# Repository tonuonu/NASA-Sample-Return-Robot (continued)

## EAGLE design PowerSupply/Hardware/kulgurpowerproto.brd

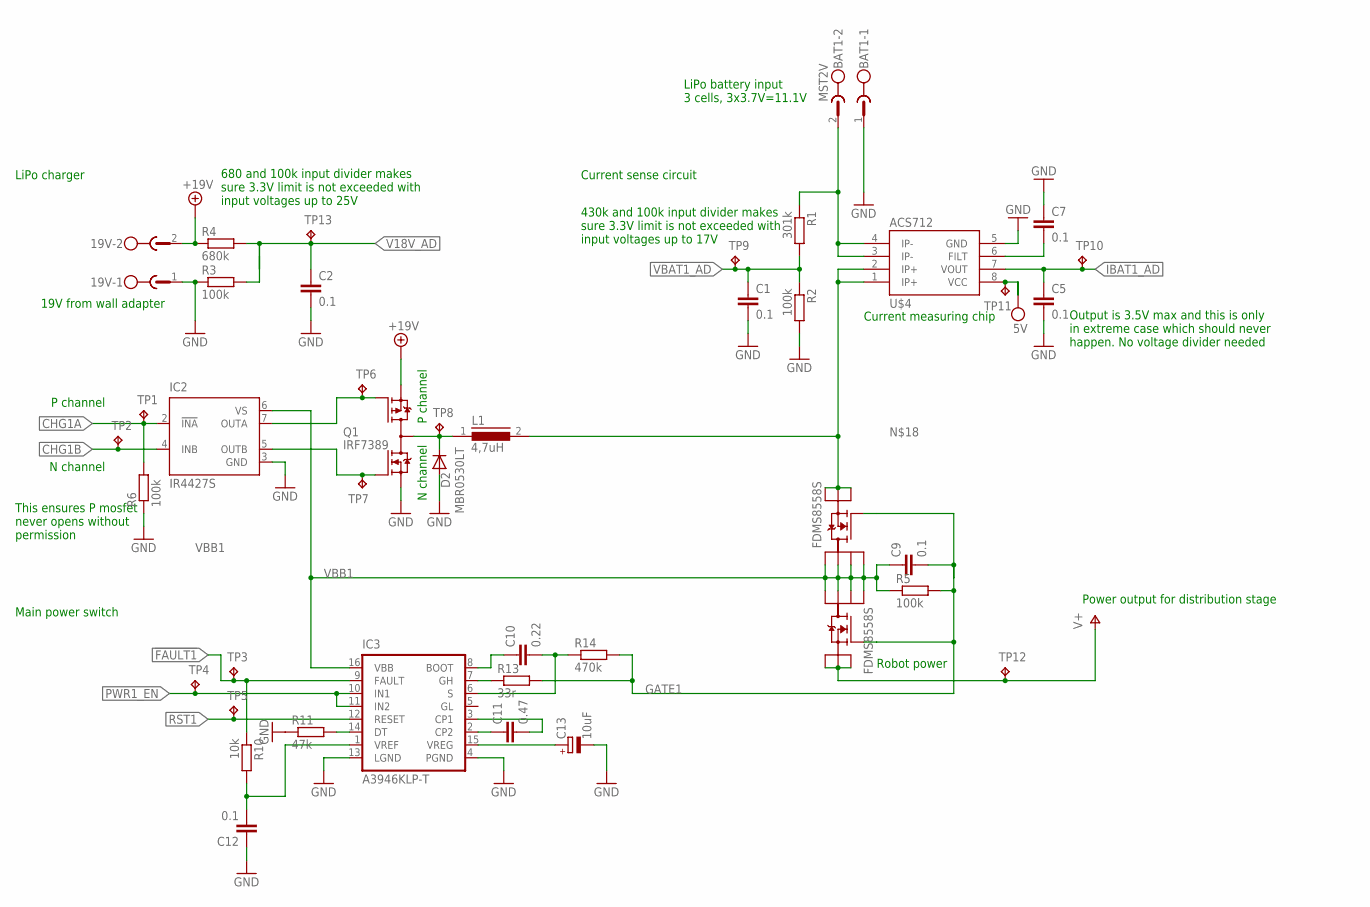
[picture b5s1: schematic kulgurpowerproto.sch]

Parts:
19V: MST2V; MSTBV2
BAT1: MST2V; MSTBV2
C1, C2, C5, C7, C9, C12: 0.1; C0603
C10: 0.22; C0603
C11: 0.47; C0603
C13: 10uF; A/3216-18R
D2: MBR0530LT; SOD123
IC2: IR4427S; SO08
IC3: A3946KLP-T; TSSOP16E
L1: 4,7uH; DR73
Q1: IRF7389; SO08-IRF
R1: 301k; R0603
R2, R3, R5, R6: 100k; R0603
R4: 680k; R0603
R10: 10k; R0603
R11: 47k; R0603
R13: 33r; R0603
R14: 470k; R0603
TP1, TP2, TP3, TP4, TP5, TP6, TP7, TP8, TP9, TP10, TP11, TP12, TP13: TPB2,54; B2,54
U$2, U$3: FDMS8558S; POWER56
U$4: ACS712; SO08

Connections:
5V: TP11.TP, U$4.8 (VCC)
!FAULT1: IC3.9 (FAULT), R10.1, TP3.TP
+19V: 19V.2, Q1.3 (P-S), R4.1
CHG1A: IC2.2 (!INA), R6.2, TP1.TP
CHG1B: IC2.4 (INB), TP2.TP
GATE1: C9.2, R5.2, R13.2, R14.2, U$2.P$4 (G), U$3.P$4 (G)
GND: 19V.1, BAT1.1, C1.2, C2.2, C5.2, C7.1, C12.1, C13.-, D2.A, IC2.3 (GND), IC3.4 (PGND), IC3.13 (LGND), Q1.1 (N-S), R2.2, R3.1, R6.1, R11.1, U$4.5 (GND)
IBAT1_AD: C5.1, TP10.TP, U$4.7 (VOUT)
unnamed: IC2.7 (OUTA), Q1.4 (P-G), TP6.TP
unnamed: IC2.5 (OUTB), Q1.2 (N-G), TP7.TP
unnamed: D2.C, L1.1, Q1.5 (D), Q1.6 (D), Q1.7 (D), Q1.8 (D), TP8.TP
unnamed: C10.1, IC3.8 (BOOT)
unnamed: L1.2, U$2.P$1 (S1), U$2.P$2 (S2), U$2.P$3 (S3), U$4.1 (IP+), U$4.2 (IP+)
unnamed: C10.2, IC3.6 (S), R14.1
unnamed: C7.2, U$4.6 (FILT)
unnamed: BAT1.2, R1.1, U$4.3 (IP-), U$4.4 (IP-)
unnamed: C11.1, IC3.2 (CP2)
unnamed: C11.2, IC3.3 (CP1)
unnamed: C12.2, IC3.1 (VREF), R10.2
unnamed: IC3.7 (GH), R13.1
unnamed: IC3.14 (DT), R11.2
unnamed: C13.+, IC3.15 (VREG)
PWR1_EN: IC3.10 (IN1), IC3.11 (IN2), TP4.TP
RST1: IC3.12 (RESET), TP5.TP
V18V_AD: C2.1, R3.2, R4.2, TP13.TP
V+: TP12.TP, U$3.P$1 (S1), U$3.P$2 (S2), U$3.P$3 (S3)
VBAT1_AD: C1.1, R1.2, R2.1, TP9.TP
VBB1: C9.1, IC2.6 (VS), IC3.16 (VBB), R5.1, U$2.P$5 (D4), U$2.P$6 (D3), U$2.P$7 (D2), U$2.P$8 (D1), U$3.P$5 (D4), U$3.P$6 (D3), U$3.P$7 (D2), U$3.P$8 (D1)

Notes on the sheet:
19V from wall adapter
LiPo battery input 3 cells, 3x3.7V=11.1V
Current measuring chip
Robot power
680 and 100k input divider makes sure 3.3V limit is not exceeded with input voltages up to 25V
430k and 100k input divider makes sure 3.3V limit is not exceeded with input voltages up to 17V
Output is 3.5V max and this is only in extreme case which should never happen. No voltage divider needed
LiPo charger
Current sense circuit
Main power switch
N channel
P channel
This ensures P mosfet never opens without permission
Power output for distribution stage

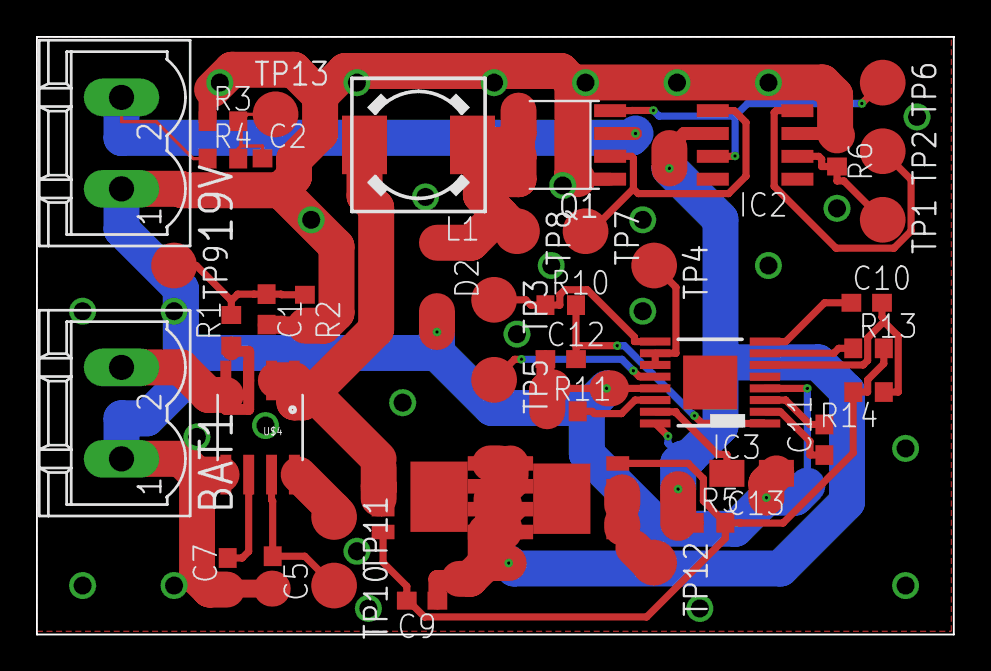
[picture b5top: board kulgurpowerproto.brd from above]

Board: 2 copper layers, 50.9 x 33.2 mm, 42 parts (0 on the bottom side), 28 nets.

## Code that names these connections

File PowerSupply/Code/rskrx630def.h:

/* Copyright (C) 2012 Renesas Electronics Corporation. All rights reserved.    */
/* Description   : Defines macros relating to the RX630 user LEDs and switches
*******************************************************************************/
/* Multiple inclusion prevention macro */
#ifndef _RSKRX630_H
#define _RSKRX630_H

/* Defines RX630 port registers */
#include "iorx630.h"

/* General Values */
#define SET_BIT_HIGH  (1)
#define SET_BIT_LOW    (0)
#define SET_BYTE_HIGH  (0xFF)
#define SET_BYTE_LOW  (0x00)

/* Switch port pins state settings */
#define  SW1          PORT3.PIDR.BIT.3
#define  SW2          PORT3.PIDR.BIT.2
#define  SW3          PORT3.PIDR.BIT.1
#define  SW4          PORT3.PIDR.BIT.0

/* LED ouptut pin settings */
#define  LED0      PORT2.PODR.BIT.B0
#define  LED1      PORT2.PODR.BIT.B1
#define  LED2      PORT2.PODR.BIT.B2
#define  LED3      PORT2.PODR.BIT.B3
#define  LED4      PORT2.PODR.BIT.B4
#define  LED5      PORT2.PODR.BIT.B5
#define  LED6      PORT2.PODR.BIT.B6
#define  LED7      PORT2.PODR.BIT.B7

/* LED data direction */
#define LED0_PORT_DIR  PORT2.PDR.BIT.B0
#define LED1_PORT_DIR  PORT2.PDR.BIT.B1
#define LED2_PORT_DIR  PORT2.PDR.BIT.B2
#define LED3_PORT_DIR  PORT2.PDR.BIT.B3
#define LED4_PORT_DIR  PORT2.PDR.BIT.B4
#define LED5_PORT_DIR  PORT2.PDR.BIT.B5
#define LED6_PORT_DIR  PORT2.PDR.BIT.B6
#define LED7_PORT_DIR  PORT2.PDR.BIT.B7

#define LED_GRN_PORT_DIR  PORT1.PDR.BIT.B3
#define LED_BLU_PORT_DIR  PORT1.PDR.BIT.B5
#define LED_RED_PORT_DIR  PORT1.PDR.BIT.B7

#define BAT0_EN PORTA.PODR.BIT.B7
#define BAT1_EN PORTB.PODR.BIT.B1
#define BAT2_EN PORTB.PODR.BIT.B2
#define BAT3_EN PORTB.PODR.BIT.B3
#define MAX1614_OFF  0
#define MAX1614_ON   1

#define BAT0_EN_DIR PORTA.PDR.BIT.B7
#define BAT1_EN_DIR PORTB.PDR.BIT.B1
#define BAT2_EN_DIR PORTB.PDR.BIT.B2
#define BAT3_EN_DIR PORTB.PDR.BIT.B3

#define PGOOD1_DIR PORT1.PDR.BIT.B9
#define PGOOD2_DIR PORTC.PDR.BIT.B2

#define PGOOD1 PORTC.PIDR.BIT.B3
#define PGOOD2 PORTC.PIDR.BIT.B2

#define OUT1_EN_DIR PORTB.PDR.BIT.B5
#define OUT2_EN_DIR PORTB.PDR.BIT.B7
#define OUT3_EN_DIR PORTJ.PDR.BIT.B3
#define OUT4_EN_DIR PORT5.PDR.BIT.B3
#define OUT5_EN_DIR PORT0.PDR.BIT.B7

#define OUT1_EN PORTB.PODR.BIT.B5
#define OUT2_EN PORTB.PODR.BIT.B7
#define OUT3_EN PORTJ.PODR.BIT.B3
#define OUT4_EN PORT5.PODR.BIT.B3
#define OUT5_EN PORT0.PODR.BIT.B7

#define SKIP0  PORTA.PODR.BIT.B1
#define SKIP1  PORTA.PODR.BIT.B2
#define SKIP2  PORTA.PODR.BIT.B3
#define SKIP3  PORTA.PODR.BIT.B5

#define SKIP0_DIR  PORTA.PDR.BIT.B1
#define SKIP1_DIR  PORTA.PDR.BIT.B2
#define SKIP2_DIR  PORTA.PDR.BIT.B3
#define SKIP3_DIR  PORTA.PDR.BIT.B5

/* Delay units */
#define uS        'u'
#define mS        'm'

/* End of multiple inclusion prevention macro */
#endif

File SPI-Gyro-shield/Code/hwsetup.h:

/*
 *  Copyright (c) 2013 Tonu Samuel
 *  All rights reserved.
 *
 *  This file is part of robot "Kuukulgur".
 *
 *  This is free software: you can redistribute it and/or modify
 *  it under the terms of the GNU General Public License as published by
 *  the Free Software Foundation, either version 3 of the License, or
 *  (at your option) any later version.
 *
 *  This is distributed in the hope that it will be useful,
 *  but WITHOUT ANY WARRANTY; without even the implied warranty of
 *  MERCHANTABILITY or FITNESS FOR A PARTICULAR PURPOSE.  See the
 *  GNU General Public License for more details.
 *
 *  You should have received a copy of the GNU General Public License
 *  along with this software.  If not, see <http://www.gnu.org/licenses/>.
 *
 */

#define myCKPOL (0)
#define myCKPH (1)
#define myIOPOL (1)

#define PD_INPUT    (0)
#define PD_OUTPUT   (1)
#define PF_TIMER    (1)
#define PF_MOTOR    (2)
#define PF_UART     (3)
#define PF_ANALOG   (0x80)

void HardwareSetup(void);

#define LED1         p1_0
#define LED1d        pd1_0
#define LED2         p1_1
#define LED2d        pd1_1
#define LED3         p1_2
#define LED3d        pd1_2
#define LED4         p1_3
#define LED4d        pd1_3
#define LED5         p1_4
#define LED5d        pd1_4

#define RESET0       p0_3
#define RESET0d      pd0_3
#define RESET1       p0_0
#define RESET1d      pd0_0
#define RESET2       p0_2
#define RESET2d      pd0_2
#define RESET3       p0_1
#define RESET3d      pd0_1

#define CDONE0       p0_7
#define CDONE1       p0_4
#define CDONE2       p0_6
#define CDONE3       p0_5

#define MOTOR_ERROR   p5_6
#define MOTOR_ERRORd   pd5_6

#define RESET5       p8_2
#define RESET5d      pd8_2


// SPI0, motor 0
#define CS0d         pd6_0
#define CS0          p6_0
#define CS0s         p6_0s
#define CLOCK0       p6_1
#define CLOCK0d      pd6_1
#define CLOCK0s      p6_1s
#define RX0          p6_2
#define RX0s         p6_2s
#define TX0          p6_3
#define TX0s         p6_3s
#define TX0d         pd6_3

// SPI3, motor 1
#define CS1d         pd4_0
#define CS1          p4_0
#define CS1s         p4_0s
#define CLOCK3       p4_1
#define CLOCK3d      pd4_1
#define CLOCK3s      p4_1s
#define RX3          p4_2
#define RX3s         p4_2s
#define RX3d         pd4_2
#define TX3          p4_3
#define TX3s         p4_3s
#define TX3d         pd4_3

// SPI4, motor 2
#define CS2         p9_4
#define CS2d        pd9_4
#define CLOCK4      p9_5
#define CLOCK4d     pd9_5
#define CLOCK4s     p9_5s
#define RX4         p9_7
#define RX4s        p9_7s
#define TX4         p9_6
#define TX4s        p9_6s
#define TX4d        pd9_6

// SPI6, motor 3
#define CS3d         pd7_3
#define CS3          p7_3
#define CS3s         p7_3s
#define CLOCK6       p4_5
#define CLOCK6d      pd4_5
#define CLOCK6s      p4_5s
#define RX6          p4_6
#define RX6s         p4_6s
#define RX6d         pd4_6
#define TX6          p4_7
#define TX6s         p4_7s
#define TX6d         pd4_7

// Serial 5

#define CS5         p8_4
#define CS5d        pd8_4
#define CS5s        p8_4s
#define CLOCK5      p7_7
#define CLOCK5d     pd7_7
#define CLOCK5s     p7_7s

#define TX5         p7_6
#define TX5s        p7_6s
#define TX5d        pd7_6
#define RX5         p8_0
#define RX5d        pd8_0
#define RX5s        p8_0s
#define TX5         p7_6
#define TX5d        pd7_6
#define TX5s        p7_6s

#define M0TX        u0tb
#define M1TX        u3tb
#define M2TX        u4tb
#define M3TX        u6tb

#define M0RX        u0rb
#define M1RX        u3rb
#define M2RX        u4rb
#define M3RX        u6rb


#define SPI_DELAY (1)


// Serial 1 (debug output)

#define TX1         p6_7
#define TX1s        p6_7s
#define TX1d        pd6_7
#define RX1         p6_6
#define RX1d        pd6_6
#define RX1s        p6_6s


struct statuses {
    char sek_flag;
};
void Read_AD(void);

extern volatile struct statuses status;
extern unsigned int base_freq;

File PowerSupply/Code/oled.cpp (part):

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#include "rskrx630def.h"

void Write_Data(unsigned char dat) {
    OLED_DC=1;
    OLED_DATA_PORT=dat;
    OLED_WR=0;
    __delay_cycles(24UL); // 0.250us
    OLED_WR=1;
    __delay_cycles(24UL); // 0.250us
    return;
}

void Write_Instruction(unsigned char cmd) {
    OLED_DC=0;
    OLED_DATA_PORT=cmd;
    OLED_WR=0;
    __delay_cycles(24UL); // 0.250us
    OLED_WR=1;
    __delay_cycles(24UL); // 0.250us
    return;
}
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
void
OLED_Set_Column_Address(unsigned char a, unsigned char b) {
    OLED_CS = 0;
    Write_Instruction(0x15);				   // Set Column Address
    Write_Data(a);					   //   Default => 0x00
    Write_Data(b);					   //   Default => 0x77
    OLED_CS = 1;
}

void
OLED_Set_Row_Address(unsigned char a, unsigned char b) {
    OLED_CS = 0;
    Write_Instruction(0x75);				   // Set Row Address
    Write_Data(a);					   //   Default => 0x00
    Write_Data(b);					   //   Default => 0x7F
    OLED_CS = 1;
}

void
OLED_Set_Write_RAM() {
    OLED_CS = 0;
    Write_Instruction(0x5C);				   // Enable MCU to Write into RAM
// omit!    OLED_CS = 1;
}

void
OLED_Set_Read_RAM() {
    OLED_CS = 0;
    Write_Instruction(0x5D);				   // Enable MCU to Read from RAM
// omit!    OLED_CS = 1;
}

void
OLED_Set_Remap_Format(unsigned char d) {
    OLED_CS = 0;
    Write_Instruction(0xA0);				   // Set Re-Map / Dual COM Line Mode
    Write_Data(d);					   //   Default => 0x40
    //     Horizontal Address Increment
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    //     Scan from COM0 to COM[N-1]
    //     Disable COM Split Odd Even
    Write_Data(0x11);				   //   Default => 0x01 (Disable Dual COM Mode)
    OLED_CS = 1;
}
void

OLED_Set_Start_Line(unsigned char d) {
    OLED_CS = 0;
    Write_Instruction(0xA1);				   // Set Vertical Scroll by RAM
    Write_Data(d);					   //   Default => 0x00
    OLED_CS = 1;
}

void
OLED_Set_Display_Offset(unsigned char d) {
    OLED_CS = 0;
    Write_Instruction(0xA2);				   // Set Vertical Scroll by Row
    Write_Data(d);					   //   Default => 0x00
    OLED_CS = 1;
}

void
OLED_Set_Display_Mode(unsigned char d) {
    OLED_CS = 0;
    Write_Instruction(0xA4 | d);				   // Set Display Mode
    //   Default => 0xA4
    //     0xA4 (0x00) => Entire Display Off, All Pixels Turn Off
    //     0xA5 (0x01) => Entire Display On, All Pixels Turn On at GS Level 15
    //     0xA6 (0x02) => Normal Display
    //     0xA7 (0x03) => Inverse Display
    OLED_CS = 1;
}

void
OLED_Set_Partial_Display(unsigned char a, unsigned char b, unsigned char c) {
    OLED_CS = 0;
    Write_Instruction(0xA8 | a);				   // Default => 0x8F
    //   Select Internal Booster at Display On
    if (a == 0x00) {
	Write_Data(b);
	Write_Data(c);
    }
    OLED_CS = 1;
}

void
OLED_Set_Function_Selection(unsigned char d) {
    OLED_CS = 0;
    Write_Instruction(0xAB);				   // Function Selection
    Write_Data(d);					   //   Default => 0x01
    //     Enable Internal VDD Regulator
    OLED_CS = 1;
}

void
OLED_Set_Display_On_Off(unsigned char d) {
    OLED_CS = 0;
    Write_Instruction(0xAE | d);				   // Set Display On/Off
    //   Default => 0xAE
    //     0xAE (0x00) => Display Off (Sleep Mode On)
    //     0xAF (0x01) => Display On (Sleep Mode Off)
    OLED_CS = 1;
}

void
OLED_Set_Phase_Length(unsigned char d) {
    OLED_CS = 0;
    Write_Instruction(0xB1);				   // Phase 1 (Reset) & Phase 2 (Pre-Charge) Period Adjustment
    Write_Data(d);					   //   Default => 0x74 (7 Display Clocks [Phase 2] / 9 Display Clocks [Phase 1])
    //     D[3:0] => Phase 1 Period in 5~31 Display Clocks
    //     D[7:4] => Phase 2 Period in 3~15 Display Clocks
    OLED_CS = 1;
}

void
OLED_Set_Display_Clock(unsigned char d) {
    OLED_CS = 0;
    Write_Instruction(0xB3);				   // Set Display Clock Divider / Oscillator Frequency
    Write_Data(d);					   //   Default => 0xD0
    //     A[3:0] => Display Clock Divider
    //     A[7:4] => Oscillator Frequency
    OLED_CS = 1;
}

void
OLED_Set_Display_Enhancement_A(unsigned char a, unsigned char b) {
    OLED_CS = 0;
    Write_Instruction(0xB4);				   // Display Enhancement
    Write_Data(0xA0 | a);				   //   Default => 0xA2
    //     0xA0 (0x00) => Enable External VSL
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    Write_Data(0x05 | b);				   //   Default => 0xB5
    //     0xB5 (0xB0) => Normal
    //     0xFD (0xF8) => Enhance Low Gray Scale Display Quality
    OLED_CS = 1;
}

void
OLED_Set_GPIO(unsigned char d) {
    OLED_CS = 0;
    Write_Instruction(0xB5);				   // General Purpose IO
    Write_Data(d);					   //   Default => 0x0A (GPIO Pins output Low Level.)
    OLED_CS = 1;
}

void
OLED_Set_Precharge_Period(unsigned char d) {
    OLED_CS = 0;
    Write_Instruction(0xB6);				   // Set Second Pre-Charge Period
    Write_Data(d);					   //   Default => 0x08 (8 Display Clocks)
    OLED_CS = 1;
}

void
OLED_Set_Precharge_Voltage(unsigned char d) {
    OLED_CS = 0;
    Write_Instruction(0xBB);				   // Set Pre-Charge Voltage Level
    Write_Data(d);					   //   Default => 0x17 (0.50*VCC)
    OLED_CS = 1;
}

void
OLED_Set_VCOMH(unsigned char d) {
    OLED_CS = 0;
    Write_Instruction(0xBE);				   // Set COM Deselect Voltage Level
    Write_Data(d);					   //   Default => 0x04 (0.80*VCC)
    OLED_CS = 1;
}

void
OLED_Set_Contrast_Current(unsigned char d) {
    OLED_CS = 0;
    Write_Instruction(0xC1);				   // Set Contrast Current
    Write_Data(d);					   //   Default => 0x7F
    OLED_CS = 1;
}

void
OLED_Set_Master_Current(unsigned char d) {
    OLED_CS = 0;
    Write_Instruction(0xC7);				   // Master Contrast Current Control
    Write_Data(d);					   //   Default => 0x0f (Maximum)
    OLED_CS = 1;
}

void
OLED_Set_Multiplex_Ratio(unsigned char d) {
    OLED_CS = 0;
    Write_Instruction(0xCA);				   // Set Multiplex Ratio
    Write_Data(d);					   //   Default => 0x7F (1/128 Duty)
    OLED_CS = 1;
}

void
OLED_Set_Display_Enhancement_B(unsigned char d) {
    OLED_CS = 0;
    Write_Instruction(0xD1);				   // Display Enhancement
    Write_Data(0x82 | d);				   //   Default => 0xA2
    //     0x82 (0x00) => Reserved
    //     0xA2 (0x20) => Normal
    Write_Data(0x20);
    OLED_CS = 1;
}

void
OLED_Set_Command_Lock(unsigned char d) {
    OLED_CS = 0;
    Write_Instruction(0xFD);				   // Set Command Lock
    Write_Data(0x12 | d);				   //   Default => 0x12
    //     0x12 => Driver IC interface is unlocked from entering command.
    //     0x16 => All Commands are locked except 0xFD.
    OLED_CS = 1;
}
const static unsigned int width = 256;
const static unsigned int height = 64;
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    unsigned int i, j;
    OLED_Set_Column_Address(OLED_Shift + a, OLED_Shift + b );
    OLED_Set_Row_Address(0,OLED_Max_Row );
    OLED_CS = 0;
    OLED_Set_Write_RAM();

    for (i = 0; i <height ; i++) { /* row */
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              Write_Data(pic[i*(width/2)+j]);
	}
    }
    OLED_CS = 1;
}

//-=-=-=-=-=-=-=-=-=-=-=-=-=-=-=-=-=-=-=-=-=-=-=-=-=-=-=-=-=-=-=-=-=-=-=
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    unsigned char i, j;
    OLED_Set_Column_Address(0x00, 0x77);
    OLED_Set_Row_Address(0x00, 0x7F);
    OLED_CS = 0;
    OLED_Set_Write_RAM();
    for (i = 0; i < 128; i++) {
	for (j = 0; j < 120; j++) {
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	    Write_Data(Data);
	}
    }
    OLED_CS = 1;
}

//-=-=-=-=-=-=-=-=-=-=-=-=-=-=-=-=-=-=-=-=-=-=-=-=-=-=-=-=-=-=-=-=-=-=-=
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    unsigned char i, j;
    OLED_Set_Column_Address(OLED_Shift + a, OLED_Shift + b);
    OLED_Set_Row_Address(c, d);
    OLED_CS = 0;
    OLED_Set_Write_RAM();
    for (i = 0; i < (d - c + 1); i++) {
	for (j = 0; j < (b - a + 1); j++) {
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	    Write_Data(Data);
	}
    }
    OLED_CS = 1;
}
#if 0
//-=-=-=-=-=-=-=-=-=-=-=-=-=-=-=-=-=-=-=-=-=-=-=-=-=-=-=-=-=-=-=-=-=-=-=
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	}
	OLED_Set_Column_Address(OLED_Shift + c, OLED_Shift + c);
	OLED_Set_Row_Address(d, d + 7);
        OLED_CS = 0;
	OLED_Set_Write_RAM();
        n=1;
        for (p = 0; p < 8; p++){
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            Write_Data(Font);
            n<<=1;
        }
        OLED_CS = 1;
	c++;
    }
    OLED_Set_Remap_Format(0x14);
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    ENABLE_PWR=1; /* Enable TPS51222. 
                   * Basically 5V is enabled to ACS712 current sensors
                   */
    OUT4_EN = 1; // Configure TPS51222 DC DC outputs
    OUT5_EN = 1; // 1 is enable, 0 is disable
#endif
    
    
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#if 1
    if(SWITCHHOLD_1 & gSwitchFlag) {
        if(OUT4_EN == 1 && ENABLE_PWR==1) {
            OUT4_EN=0;
            OUT5_EN=0;
           // ENABLE_PWR=0;
        } else if(ENABLE_PWR==0) {
            ENABLE_PWR=1;
        } else {
            OUT4_EN = 1;
            OUT5_EN = 1;
            gSwitchFlag &= (SWITCHPRESS_ALL | ~SWITCHHOLD_1);
            gSwitchFlag |= SWITCHPRESS_1;
        }
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    OLED_RD_PORT_DIR=1;
    OLED_RESET_PORT_DIR=1;
    PORTD.PDR.BYTE=0xFF;
    OLED_CS=1;
    OLED_WR=1;
    OLED_RD=1;

    OLED_RESET = 0;    
    __delay_cycles(100UL*2000UL); // 2000us delay - required in datasheet
    OLED_RESET = 1;
    __delay_cycles(100UL*2000UL); // 2000us delay    

    OLED_Set_Command_Lock(0x12);			   // Unlock Basic Commands (0x12/0x16)
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
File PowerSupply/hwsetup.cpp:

/* Copyright (C) 2012 Renesas Electronics Corporation. All rights reserved.   */
/*******************************************************************************
* File Name    : hwsetup.c
* Version     : 1.00
* Device     : R5F5630E
* Tool-Chain   : Renesas RX Toolchain 1.2.0.0
* H/W Platform  : RSKRX630
* Description   : Defines the hardware initialisation routines used each time 
*          the MCU is restarted. 
*******************************************************************************/
/*******************************************************************************
* History     : 23 Jan. 2012  Ver. 1.00 First Release
*******************************************************************************/

/*******************************************************************************
System Includes
*******************************************************************************/
/* Includes assembley level definitions */
#include    <machine.h>
/* Following header file provides C99 type definitions. */
#include <stdint.h>

/*******************************************************************************
User Includes (Project Level Includes)
*******************************************************************************/
/* Defines RX630 port registers */
#include "iorx630.h"
/* Defines macros relating to the RX630 user LEDs and switches */
#include "rskrx630def.h"
/* LCD controlling function prototypes & macro definitions */
#include "oled.h"
/* Switch handler function definitions */
#include "switch.h"
/* Contains declarations for the functions defined in this file */
#include "hwsetup.h"

/*******************************************************************************
* Outline     : HardwareSetup
* Description   : Contains all the setup functions called at device restart
* Argument      : none
* Return value  : none
*******************************************************************************/
void HardwareSetup(void)
{
  ConfigureOperatingFrequency();
  ConfigureOutputPorts();
  ConfigureInterrupts();
  EnablePeripheralModules();
}
/*******************************************************************************
* End of function HardwareSetup
*******************************************************************************/

/*******************************************************************************
* Outline     : ConfigureOperatingFrequency
* Description   : Configures the clock settings for each of the device clocks
* Argument      : none
* Return value  : none
*******************************************************************************/
void ConfigureOperatingFrequency(void)
{      
  /* Declare and initialise a loop count variable */
  uint16_t i = 0;
    
  /* Protection off */
  SYSTEM.PRCR.WORD = 0xA503;      
  
  /* Stop sub-clock */
  SYSTEM.SOSCCR.BYTE = 0x01;      
                    
  /* Specify a wait state greater than 10ms at 12MHz (10.92 msec) */ 
  SYSTEM.MOSCWTCR.BYTE = 0x0D;    
    
  /* 4194304 state (default)*/
  /* wait over 12ms  @PLL=192MHz(12MHz*16) */                
  SYSTEM.PLLWTCR.BYTE = 0x0F;      
  
  /* x16 @PLL */
  SYSTEM.PLLCR.WORD = 0x0F00;  
  
  /* Configure the EXTAL pin */
  PORT3.PMR.BIT.B6 = 0;
  PORT3.PDR.BIT.B6 = 0;

  /* Configure the XTAL pin */
  PORT3.PMR.BIT.B7 = 0;
  PORT3.PDR.BIT.B7 = 0;    

  /* Turn on EXTAL */
  SYSTEM.MOSCCR.BYTE = 0x00;  
      
  /* Turn on the PLL and enable writing to the PLL control register */
  SYSTEM.PLLCR2.BYTE = 0x00;  
  
  /* Wait over 12ms */
  for(i=0; i<2075; i++)
  {
    nop();
  }
    
  /* Configure the clocks as follows -
  Clock Description              Frequency
  ----------------------------------------
  PLL Clock frequency...............192MHz
  System Clock Frequency.............96MHz
  Peripheral Module Clock B..........48MHz   
  FlashIF Clock......................48MHz
  External Bus Clock.................48MHz */       
  SYSTEM.SCKCR.LONG = 0x21821211; 
//  SYSTEM.SCKCR.BIT.BCK=6; // Change bus speed to lower, /64 divisor 
//  SYSTEM.SCKCR.BIT.PSTOP1=1; // Disable BCLK pin, it is useless for us;
  
  /* Configure the clocks as follows -
  Clock Description              Frequency
  ----------------------------------------
  USB Clock..........................48MHz    
  IEBus Clock........................24MHz */ 
  SYSTEM.SCKCR2.WORD = 0x0033;
  
  /* Set the clock source to PLL */
  SYSTEM.SCKCR3.WORD = 0x0400;
  
  /* Protection on */
  SYSTEM.PRCR.WORD = 0xA500;    
}
/*******************************************************************************
* End of function ConfigureOperatingFrequency
*******************************************************************************/

/*******************************************************************************
* Outline     : ConfigureOutputPorts
* Description   : Configures the port and pin direction settings, and sets the
*          pin outputs to a safe level.
* Argument    : none
* Return value  : none
*******************************************************************************/
void ConfigureOutputPorts(void)
{  

    /* Configure the LED pins (LED0-LED3) as outputs */
  LED0_PORT_DIR = 0x1;
  LED1_PORT_DIR = 0x1;

  /* Set LED pin outputs as high (all LEDs off) */
  LED0 = LED_OFF;
  LED1 = LED_OFF;

}
/*******************************************************************************
* End of function ConfigureOutputPorts
*******************************************************************************/

/*******************************************************************************
* Outline     : ConfigureInterrupts
* Description   : Configures the interrupts used
* Argument    : none
* Return value  : none
*******************************************************************************/
void ConfigureInterrupts(void)
{
  /* Configure switch interrupts */
  InitialiseSwitchInterrupts();
}
/*******************************************************************************
* End of function ConfigureInterrupts
*******************************************************************************/

/*******************************************************************************
* Outline     : EnablePeripheralModules
* Description   : Enables and configures peripheral devices on the MCU
* Argument    : none
* Return value  : none
*******************************************************************************/
void EnablePeripheralModules(void)
{
  /* Peripherals initialised in specific initialisation functions */
}
/*******************************************************************************
* End of function EnablePeripheralModules
*******************************************************************************/

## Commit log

2013-10-19 Some basic code in
2013-10-27 new power supply initial code commit
2013-11-09 Heartbeat works
2013-11-09 5 x SPI skeleton in
2013-11-09 Cleanups
2013-11-09 TX interrupt skeletons added
2013-11-10 Work on SPI system
2013-11-10 Clarifications
2013-11-10 spi5 receive interrupt works!
2013-11-10 CS seems to trigger INT1 now.
2013-11-18 OLED works
2013-11-19 OLED logo ok
2013-11-21 Cleanups etc
2013-11-24 Re-organizing code
2013-11-24 Eagle files in
2013-11-24 .gitignore to ignore eagle backups
2013-11-25 More schematics in
2013-12-01 Lot of changes to schematics. A lot.
2013-12-01 Little cosmetics on code too
2013-12-07 lot of work done on schematics
2013-12-08 More work on electronics
2013-12-08 PWM code fixes
2013-12-09 Converted into 2 layer board from 4 layer. Seems to be OK for production
2013-12-10 Silkscreen fixes
2013-12-14 Minor bugfixes to boards.
2013-12-14 Seems I got SPI signalling now right
2013-12-15 Fully interrupt driven solution was too slow. Rewrote to main loop state machine way.
2013-12-15 Clarifications in schematic
2013-12-15 CDONE should be without pullup
2013-12-15 Another bugfix
2013-12-22 cleanup
2013-12-22 Wait for data transmissions to end before letting CS go high Enable fast interrupt for UART5 RX
2013-12-23 Minor fixes
2013-12-23 Minor fixes to PCB
2013-12-23 Garbage cleanup
2013-12-29 New version of Arduino shield implemented
2013-12-29 Shield code updates
2014-01-01 New hardware revision needs some fixes
2014-01-01 header added
2014-01-01 GPL licences added
2014-01-01 Switch stuff modified for 4 switches RGB LED PWM stuff modified
2014-01-01 Cosmetic fixes to switch logic
2014-01-04 Lot of different small things done in code
2014-01-05 ADC works POWER_EN works
2014-01-05 ADC does now 4 times measurement in hardware and averages result. Battery enable outputs are configured
2014-01-05 Imon1, Imon2 inputs done temperature stuff removed Adapter voltage measurement done ADC12 averaging added Out1...out5 configuration added
2014-01-05 Two resistors in ladder were swapped Nominals rised for pullup. Next power bill will be smaller!
2014-01-13 Misc fixes about ADCs Basic menu system implemented Clarifications about MAX1614 driving basic errorlog implementation
2014-01-13 MCU board version 3
2014-01-13 Powersupply main board new version added
2014-01-18 Misc fixes of nominals
2014-01-18 Gyroscope code addad. Nonworking yet.
2014-01-24 SPI2 instead of SPI6 now. P7_0 and P7_1 are open collector outputs only and not fit for our work.
2014-01-24 New shield PCB version.
2014-01-24 Cosmetics
2014-01-24 Both gyros work on basic level
2014-01-24 Gyros, step 2
2014-01-25 USB stuff added in minimal demo
2014-01-25 More clarifications and cleanups
2014-01-25 shell() added
2014-01-26 gyro on usb works
2014-01-26 Misc USB shell fixes
2014-01-26 Cleanup & clarification MEMS screen is now updated fast
2014-01-26 clarification
2014-01-26 Now regular interrupt is ran 1000 times per second. Timings are fixed, so we have plenty of free time. Gyroscope settings are fixed.
2014-01-26 Oops, removed too much.
2014-02-11 Clarifications and cleanups Acceleration command stuff added
2014-02-11 Cleanup, clarification
2014-02-13 Shield PCB as ordered in.
2014-02-13 Never MCU board of power supply in. 19.2Mhz oscillator added
2014-02-13 New lower PCB of power supply in
2014-02-14 more clarification and safety
2014-02-14 cleanup/clarification
2014-02-14 more clarification
2014-02-14 This version seems to work
2014-02-19 Things like this for steering servos:
    robot:/#
    robot:/# setsteering 0 0
    robot:/# setsteering 100 100
    robot:/# setsteering -100 1
    robot:/# setsteering -100 -100
    robot:/#
2014-02-19 date setting added robot:/# date 19/2/2014 3 22:00:00 Set date to: 19/02/0014 3 22:00:00
    robot:/#
2014-02-27 Steering servo current measuring UI and calculations fixed, maximum value now always known. Added screen to manage steering power supply Added Power Good info. Extended steering servo range
2014-03-31 Returning ACS712 correct constant
2014-03-31 Setsteering off implemented Steering angle is wider now Disable automatic start of servo PWMs
2014-03-31 New versions of PCBs in. This version went to Seeedstudio order
2014-04-10 Seems that finally I got it right. Ticks and other info is computed properly.
2014-04-10 More fixes on motor issues
2014-04-10 Acceleration implemented
2014-04-10 Old code removed
2014-04-10 Garbage cleaning
2014-04-10 Added support for different motors having different currend commands (CMD_SPEED or CMD_ACCELERATION)
2014-04-10 Fixed a syntax error
2014-04-10 Implemented CMD_GET_CUR_TARGET_SPEED; also CMD_SPEED/CMD_ACCELERATION now return cur target speed (even though the Arduino code currently does not use it)
2014-04-10 PCB updates
2014-04-10 typo fix unneccessary delay removed
2014-04-10 Fixed a bug
2014-04-11 Make RESET on INT0 Clarification
2014-04-11 Misc schematic clarifications
2014-04-11 Equalize naming of serial ports and their control pins
2014-04-19 TX5 pin is now PD_INPUT for most of the time, to be changed to PD_OUTPUT only for brief periods when needed
2014-04-19 Changed SPI5 motor load/switchcount protocol to be the same as in motor controller protocol
2014-04-19 Added debugging code
2014-04-19 Fixed debugging code
2014-04-19 Fixed compiler errors
2014-04-19 Fixed a compiler warning
2014-04-19 Fixed a bug where SPI5 receive stopped after any SPI5 transaction with CS5 HIGH
2014-04-19 Removed debugging code
2014-04-19 Changed motor controller reset logic
2014-04-19 Debugging change: commented out send_cur_cmd()
2014-04-19 Undo debugging change: commented out send_cur_cmd()
2014-04-19 Simplified motor tickcount and load calculations
2014-04-19 Hopefully fixed complete_*tx() handling in send_cur_cmd() for RX bytes
2014-04-19 Again, hopefully fixed complete_*tx() handling in send_cur_cmd() for RX bytes
2014-04-19 For motors that are not ready, consider voltage/load/ticks/cur_speed to be all 0
2014-04-19 Added a 100ms delay to the end of motor controller reset procedure, as apparently motor controller reports garbage values during that period
2014-04-19 For motors that report voltage=0, consider load/ticks/cur_speed to be all 0
2014-04-19 get_voltage() is now done before send_cur_cmd(), to detect failed motors (voltage=0) earlier
2014-04-19 Reverted change "Added a 100ms delay to the end of motor controller reset procedure, as apparently motor controller reports garbage values during that period"
2014-04-19 Reduced the length of time when interrupts are disabled in receive_ticks()
2014-04-19 Remed disabling of intrerrupts while FPGA code is downloaded
2014-04-20 Schematic component type fixes
2014-04-20 Motor controller reset procedure now waits until all motors report nonzero voltage (max wait 300ms)
2014-04-20 Minor refactoring
2014-04-20 voltage and cur_target_speed are now reported to SPI5 as median of last 3 values
2014-04-20 Motor status LEDs now use motor_online[] flags instead of CDONE*
2014-04-20 Some values changed in schematic
2014-04-20 Voltage 0xffff is now considered invalid, just like voltage 0
2014-04-20 Fixed voltage 0xffff check
2014-04-20 Motor controller reset is now triggered based on motor_online[] instead of CDONE*
2014-04-20 Reordered pin definitions to be more logical
2014-04-23 After downloading FPGA image to motor controllers, send CMD_SPEED repeatedly to workaround a motor controller bug
2014-04-23 Fixed a recently introduced bug that shortened motor valid voltage wait cycle
2014-04-23 Added automatic detection of motor IDs, allowing any motor to be connected to any UART socket
2014-04-23 Fixed a bug when setting backup UART_to_motor_id[] values
2014-04-23 Renamed CDONEx numbers to correspond to the same ordering as CSx/MxTX/MxRX/motor_id
2014-04-23 Fixed a bug where CDONE checks did not use UART_to_motor_id[]
2014-05-14 Cleanup, indent Mode switch added New current formula for imon1/2 More tolerant to little overvoltage Chargers have faster, 30kHz PWM now
2014-05-14 Output enable debug code
2014-05-14 PCB/sch small changes. 19.2Mhz fix additional transistor PSU resistor fixes
2014-05-19 Values changed
2014-05-19 Start PC initially setpower command added
2014-05-19 cat /switch implemented
2014-05-20 Enable all outputs at once
2014-05-21 Changed comments
2014-05-21 Motors are now reset and FPGA image sent only when all motors are stopped, and max once in 30 seconds
2014-05-21 Converted C++ syntax to C
2014-05-22 Refactored dangerous code
2014-05-22 Fixed a bug in all_motors_stopped handling
2014-05-24 turn off current protection
2014-05-24 5V is important
2014-05-30 AD input and interrupt are much faster now RGB LED code is better slightly DA code added
2014-05-31 Show adapter voltage on OLED Disable current indication if battery is not connected. Otherwise they show 8.8A because lack of 5V on current sensors
2014-05-31 Add RGB status NONE
2014-05-31 !SKIP0..!SKIP3 port configuration added
2014-05-31 Shell command cat /power/status added
2014-05-31 Charging solution. Does not work yet :(
2014-06-08 indent
2014-06-09 PGOOD problems are detected and fix attempted ADC now makes 4 readings and averages their value instead of 1 reading Before making suicide OLED is updated, red LED is lit
2014-06-09 Debugging 3Mbps serial interface added to Renesas shield code Competition standard motor controller FPGA image included
2014-06-13 NASA level 1 (2nd try) (whistling)
